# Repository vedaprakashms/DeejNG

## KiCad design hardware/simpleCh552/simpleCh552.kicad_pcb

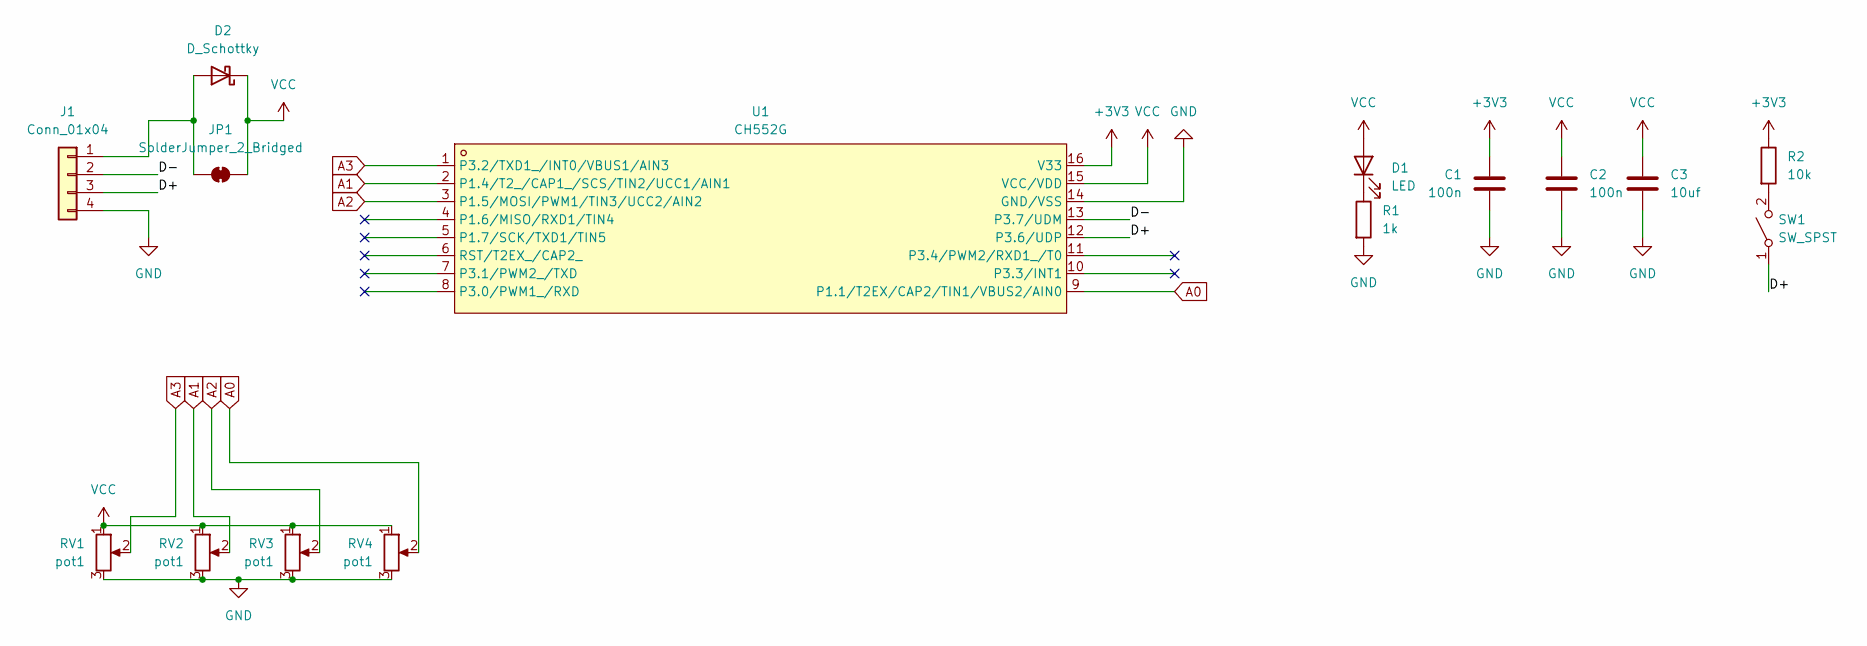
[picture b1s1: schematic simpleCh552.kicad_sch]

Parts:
C1, C2: 100n; C_0603_1608Metric
C3: 10uf; C_0805_2012Metric
D1: LED; LED_1206_3216Metric
D2: D_Schottky; D_SMA_Handsoldering
J1: Conn_01x04; PinSocket_1x04_P2.54mm_Vertical
JP1: SolderJumper_2_Bridged; SolderJumper-2_P1.3mm_Bridged2Bar_RoundedPad1.0x1.5mm
R1: 1k; R_1206_3216Metric
R2: 10k; R_1206_3216Metric
RV1, RV2, RV3, RV4: pot1; Potentiometer_Omeg_PC16BU_Vertical
SW1: SW_SPST; SW_Tactile_SPST_NO_Straight_CK_PTS636Sx25SMTRLFS
U1: CH552G; SOP-16_L10.0-W3.9-P1.27-LS6.0-BL; LCSC Part C111292

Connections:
+3V3: C1.1, R2.1, U1.16 (V33)
/D+: J1.3, SW1.1 (A), U1.12 (P3.6/UDP)
/D-: J1.2, U1.13 (P3.7/UDM)
A0: RV4.2, U1.9 (P1.1/T2EX/CAP2/TIN1/VBUS2/AIN0)
A1: RV2.2, U1.2 (P1.4/T2_/CAP1_/SCS/TIN2/UCC1/AIN1)
A2: RV3.2, U1.3 (P1.5/MOSI/PWM1/TIN3/UCC2/AIN2)
A3: RV1.2, U1.1 (P3.2/TXD1_/INT0/VBUS1/AIN3)
GND: C1.2, C2.2, C3.2, J1.4, R1.2, RV1.3, RV2.3, RV3.3, RV4.3, U1.14 (GND/VSS)
unnamed: D1.1 (K), R1.1
unnamed: D2.2 (A), J1.1, JP1.1 (A)
unnamed: R2.2, SW1.2 (B)
VCC: C2.1, C3.1, D1.2 (A), D2.1 (K), JP1.2 (B), RV1.1, RV2.1, RV3.1, RV4.1, U1.15 (VCC/VDD)

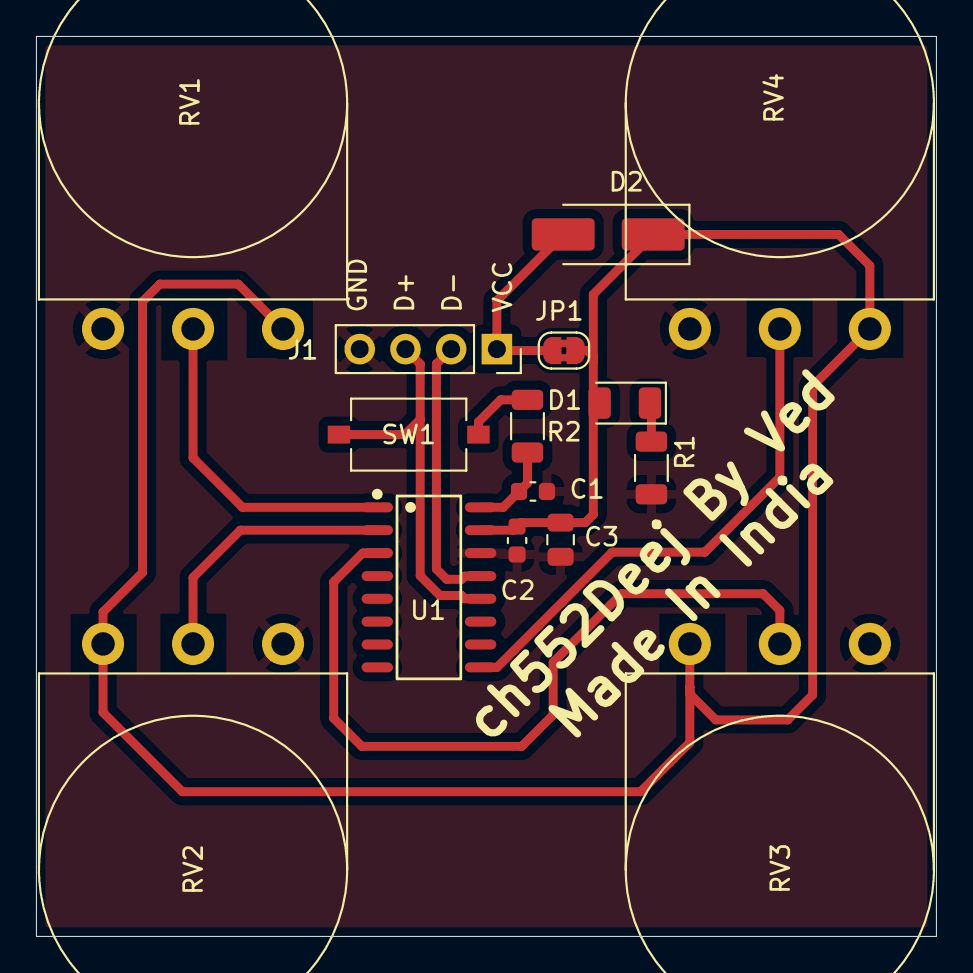
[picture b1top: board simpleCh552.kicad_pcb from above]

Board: 2 copper layers, 50.0 x 50.0 mm, 15 parts (0 on the bottom side), 12 nets.

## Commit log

2026-01-02 new firmware and board
